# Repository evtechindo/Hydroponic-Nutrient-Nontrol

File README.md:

# Hydroponic-Nutrient-Nontrol
Hydroponic Nutrient Control

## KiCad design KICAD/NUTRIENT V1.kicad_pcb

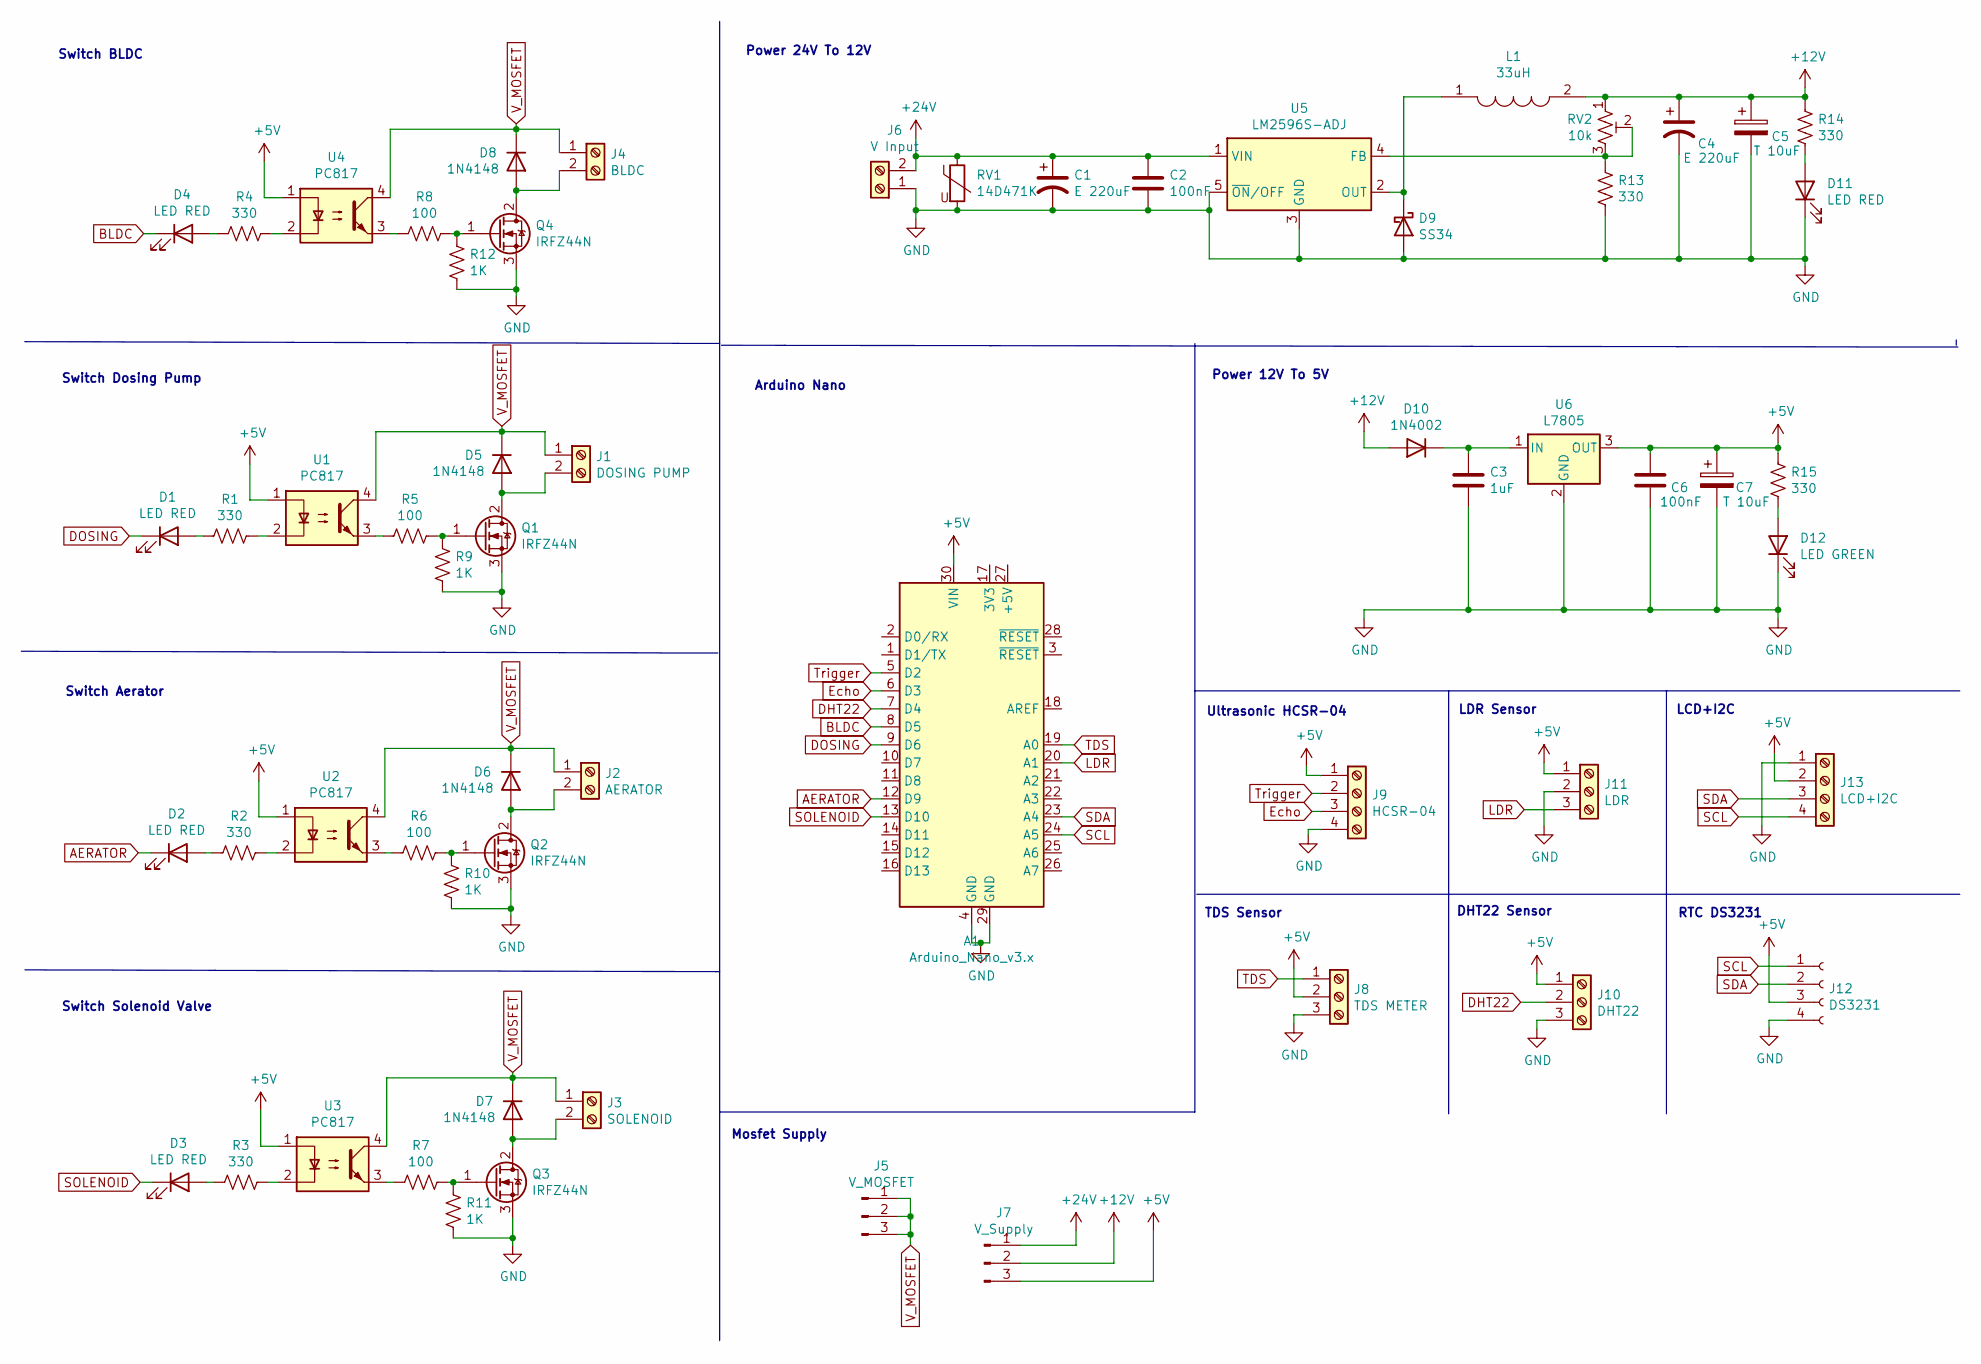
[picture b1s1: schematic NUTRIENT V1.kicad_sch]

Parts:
A1: Arduino_Nano_v3.x; Arduino_Nano
C1, C4: E 220uF; CP_Elec_10x10
C2, C6: 100nF; C_0805_2012Metric_Pad1.18x1.45mm_HandSolder
C3: 1uF; C_0805_2012Metric_Pad1.18x1.45mm_HandSolder
C5, C7: T 10uF; C_1206_3216Metric_Pad1.33x1.80mm_HandSolder
D1, D2, D3, D4, D11: LED RED; LED_D3.0mm
D5, D6, D7, D8: 1N4148; D_DO-35_SOD27_P7.62mm_Horizontal
D9: SS34; D_SMA
D10: 1N4002; D_DO-41_SOD81_P10.16mm_Horizontal
D12: LED GREEN; LED_D3.0mm
J1: DOSING PUMP; TerminalBlock_Phoenix_MKDS-1,5-2-5.08_1x02_P5.08mm_Horizont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
J2: AERATOR; TerminalBlock_Phoenix_MKDS-1,5-2-5.08_1x02_P5.08mm_Horizont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
J3: SOLENOID; TerminalBlock_Phoenix_MKDS-1,5-2-5.08_1x02_P5.08mm_Horizont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
J4: BLDC; TerminalBlock_Phoenix_MKDS-1,5-2-5.08_1x02_P5.08mm_Horizont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
J5: V_MOSFET; PinHeader_1x03_P2.54mm_Vertical
J6: V Input; TerminalBlock_Phoenix_MKDS-1,5-2-5.08_1x02_P5.08mm_Horizont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
J7: V_Supply; PinHeader_1x03_P2.54mm_Vertical
J8: TDS METER; TerminalBlock_Phoenix_MKDS-1,5-3-5.08_1x03_P5.08mm_Horizont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
J9: HCSR-04; TerminalBlock_Phoenix_MKDS-1,5-4-5.08_1x04_P5.08mm_Horizont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
J10: DHT22; TerminalBlock_Phoenix_MKDS-1,5-3-5.08_1x03_P5.08mm_Horizont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
J11: LDR; TerminalBlock_Phoenix_MKDS-1,5-3-5.08_1x03_P5.08mm_Horizont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
J12: DS3231; PinSocket_1x04_P2.54mm_Horizontal
J13: LCD+I2C; TerminalBlock_Phoenix_MKDS-1,5-4-5.08_1x04_P5.08mm_Horizont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
L1: 33uH; L_10.4x10.4_H4.8; Manufacturer_Part_Number CDRH104RNP-470NC; Mouser Part Number 851-CDRH104RNP-470NC
Q1, Q2, Q3, Q4: IRFZ44N; TO-263-2
R1, R2, R3, R4, R13, R14, R15: 330; R_1206_3216Metric_Pad1.30x1.75mm_HandSolder
R5, R6, R7, R8: 100; R_1206_3216Metric_Pad1.30x1.75mm_HandSolder
R9, R10, R11, R12: 1K; R_1206_3216Metric_Pad1.30x1.75mm_HandSolder
RV1: 14D471K; RV_Disc_D12mm_W7.9mm_P7.5mm
RV2: 10k; Potentiometer_Bourns_3296W_Vertical
U1, U2, U3, U4: PC817; DIP-4_W7.62mm
U5: LM2596S-ADJ; TO-263-5_TabPin3
U6: L7805; TO-263-2

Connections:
+5V: A1.30 (VIN), C6.1, C7.1, J7.3, J8.2, J9.1, J10.1, J11.1, J12.3, J13.2, R15.1, U1.1, U2.1, U3.1, U4.1, U6.3 (OUT)
+12V: C4.1, C5.1, D10.2 (A), J7.2, L1.2, R14.1, RV2.1
+24V: C1.1, C2.1, J6.2, J7.1, RV1.1, U5.1 (VIN)
AERATOR: A1.12 (D9), D2.1 (K)
BLDC: A1.8 (D5), D4.1 (K)
DHT22: A1.7 (D4), J10.2
DOSING: A1.9 (D6), D1.1 (K)
Echo: A1.6 (D3), J9.3
GND: A1.4 (GND), A1.29 (GND), C1.2, C2.2, C3.2, C4.2, C5.2, C6.2, C7.2, D9.2 (A), D11.1 (K), D12.1 (K), J6.1, J8.3, J9.4, J10.3, J11.2, J12.4, J13.1, Q1.3 (S), Q2.3 (S), Q3.3 (S), Q4.3 (S), R9.1, R10.1, R11.1, R12.1, R13.2, RV1.2, U5.3 (GND), U5.5 (~ON/OFF), U6.2 (GND)
LDR: A1.20 (A1), J11.3
unnamed: C3.1, D10.1 (K), U6.1 (IN)
unnamed: D1.2 (A), R1.2
unnamed: D2.2 (A), R2.2
unnamed: D3.2 (A), R3.2
unnamed: D4.2 (A), R4.2
unnamed: D5.2 (A), J1.2, Q1.2 (D)
unnamed: D6.2 (A), J2.2, Q2.2 (D)
unnamed: D7.2 (A), J3.2, Q3.2 (D)
unnamed: D8.2 (A), J4.2, Q4.2 (D)
unnamed: D9.1 (K), L1.1, U5.2 (OUT)
unnamed: D11.2 (A), R14.2
unnamed: D12.2 (A), R15.2
unnamed: Q1.1 (G), R5.1, R9.2
unnamed: Q2.1 (G), R6.1, R10.2
unnamed: Q3.1 (G), R7.1, R11.2
unnamed: Q4.1 (G), R8.1, R12.2
unnamed: R1.1, U1.2
unnamed: R2.1, U2.2
unnamed: R3.1, U3.2
unnamed: R4.1, U4.2
unnamed: R5.2, U1.3
unnamed: R6.2, U2.3
unnamed: R7.2, U3.3
unnamed: R8.2, U4.3
unnamed: R13.1, RV2.2, RV2.3, U5.4 (FB)
SCL: A1.24 (A5), J12.1, J13.4
SDA: A1.23 (A4), J12.2, J13.3
SOLENOID: A1.13 (D10), D3.1 (K)
TDS: A1.19 (A0), J8.1
Trigger: A1.5 (D2), J9.2
V_MOSFET: D5.1 (K), D6.1 (K), D7.1 (K), D8.1 (K), J1.1, J2.1, J3.1, J4.1, J5.1, J5.2, J5.3, U1.4, U2.4, U3.4, U4.4

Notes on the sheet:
RTC DS3231
Switch BLDC
Switch Aerator
TDS Sensor
Switch Dosing Pump
LCD+I2C
Power 24V To 12V
Mosfet Supply
Arduino Nano
Switch Solenoid Valve
Power 12V To 5V
Ultrasonic HCSR-04
LDR Sensor
DHT22 Sensor

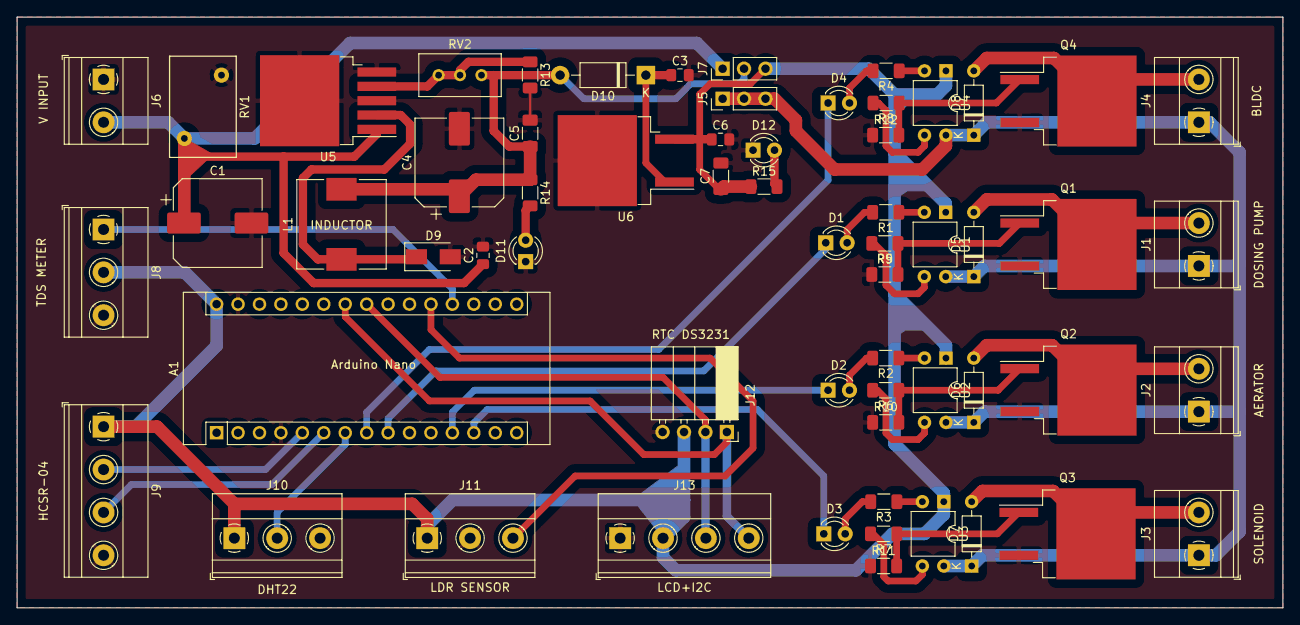
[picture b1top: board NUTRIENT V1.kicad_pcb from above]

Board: 2 copper layers, 150.0 x 70.0 mm, 61 parts (0 on the bottom side), 41 nets.

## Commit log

2023-02-05 Menambahkan Desain Schematik & Layout
2023-02-05 Menambahkan Code & Simlation
